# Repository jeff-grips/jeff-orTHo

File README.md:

# jeff-orTHo
 through-hole ortho board

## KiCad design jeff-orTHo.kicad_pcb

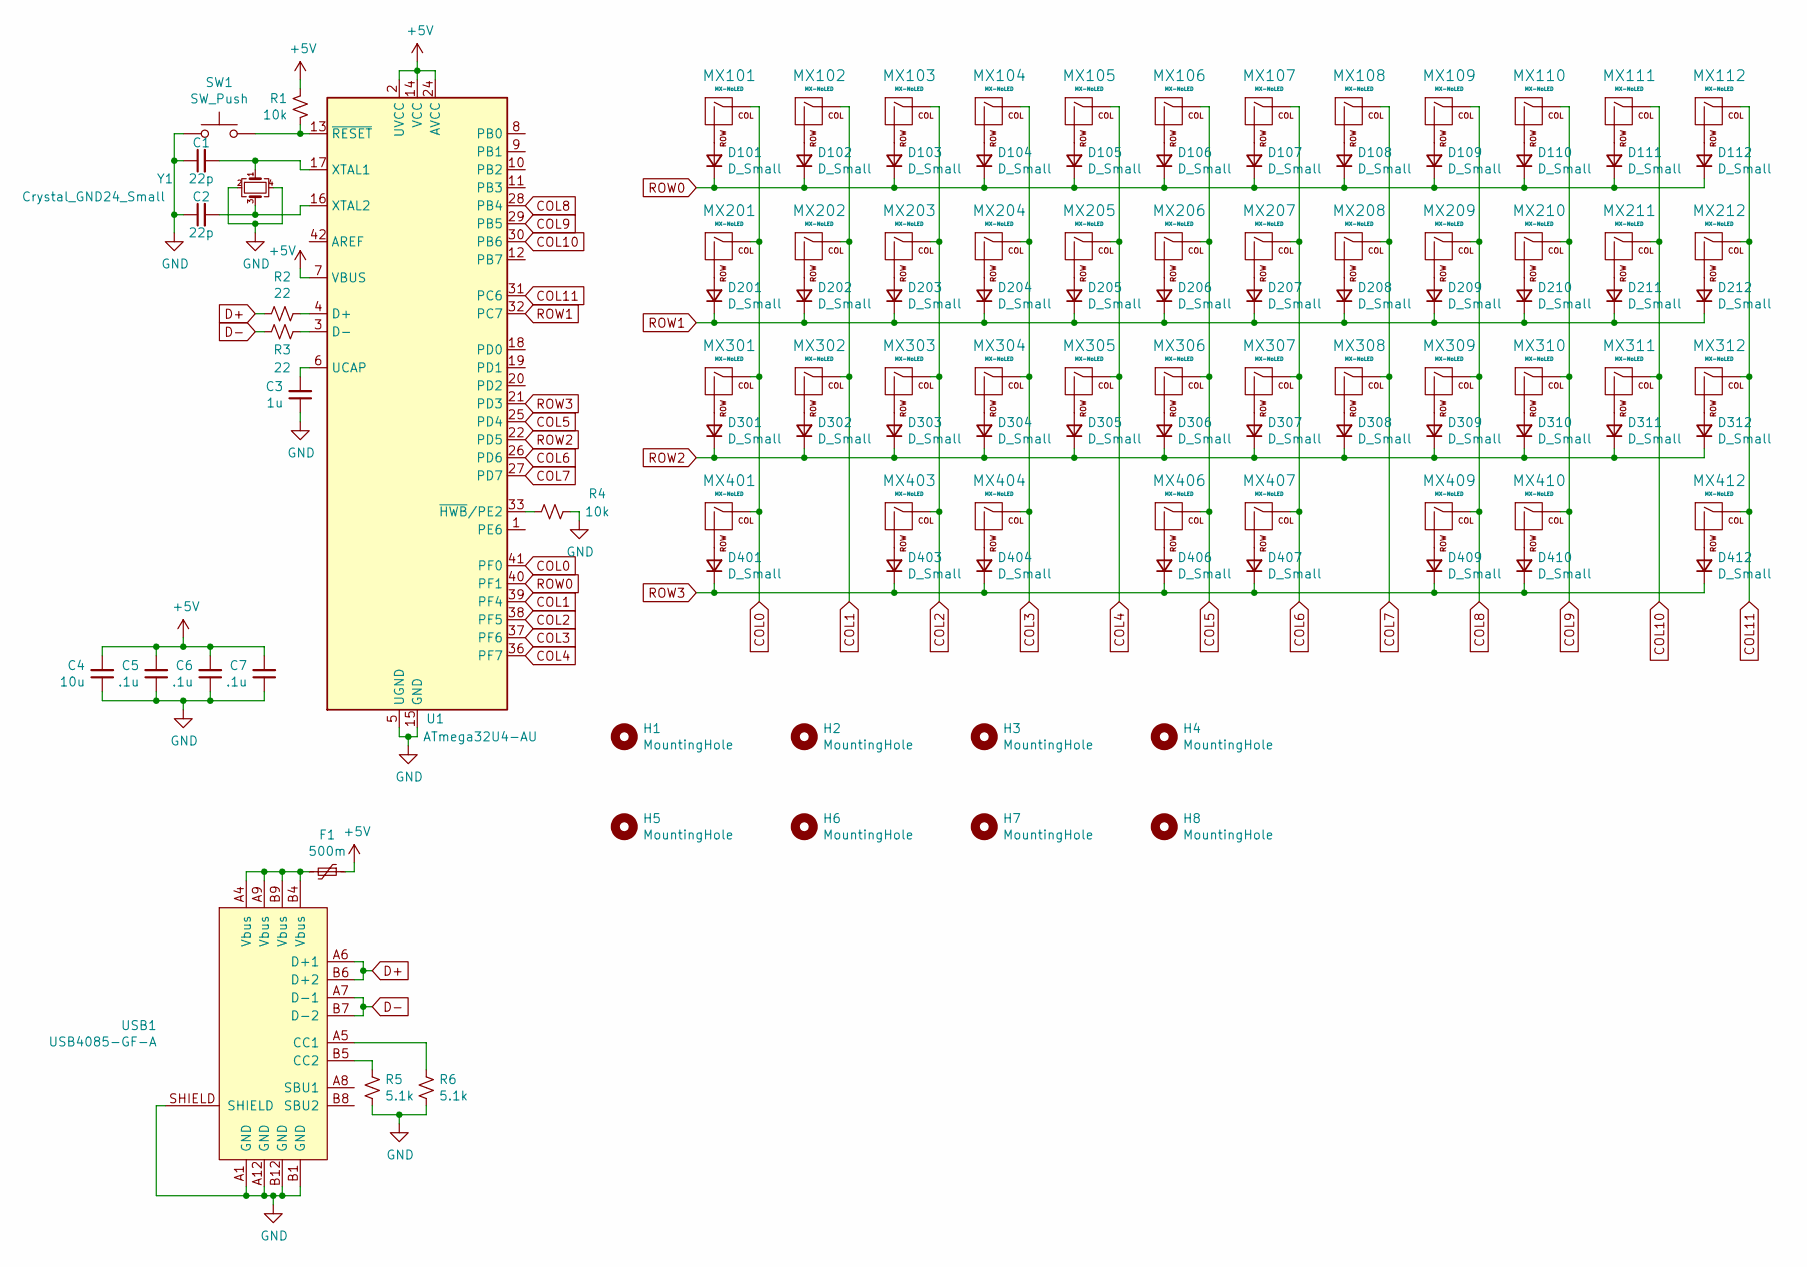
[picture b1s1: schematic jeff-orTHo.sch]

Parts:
C1, C2: 22p; C_1206_3216Metric_Pad1.33x1.80mm_HandSolder
C3: 1u; C_1206_3216Metric_Pad1.33x1.80mm_HandSolder
C4: 10u; C_1206_3216Metric_Pad1.33x1.80mm_HandSolder
C5, C6, C7: .1u; C_1206_3216Metric_Pad1.33x1.80mm_HandSolder
D101, D102, D103, D104, D105, D106, D107, D108, D109, D110, D111, D112, D201, D202, D203, D204, D205, D206, D207, D208, D209, D210, D211, D212, D301, D302, D303, D304, D305, D306, D307, D308, D309, D310, D311, D312, D401, D403, D404, D406, D407, D409, D410, D412: D_Small; D_SOD-123
F1: 500m; Fuse_1206_3216Metric_Pad1.42x1.75mm_HandSolder
H1, H2, H3, H4, H5, H6, H7, H8: MountingHole; MountingHole_2.2mm_M2
MX101, MX102, MX103, MX104, MX105, MX106, MX107, MX108, MX109, MX110, MX111, MX112, MX201, MX202, MX203, MX204, MX205, MX206, MX207, MX208, MX209, MX210, MX211, MX212, MX301, MX302, MX303, MX304, MX305, MX306, MX307, MX308, MX309, MX310, MX311, MX312: MX-NoLED; MX-1U-NoLED
MX401, MX403, MX404, MX406, MX407, MX409, MX410, MX412: MX-NoLED; MX-1.5U-NoLED
R1, R4: 10k; R_1206_3216Metric_Pad1.30x1.75mm_HandSolder
R2, R3: 22; R_1206_3216Metric_Pad1.30x1.75mm_HandSolder
R5, R6: 5.1k; R_1206_3216Metric_Pad1.30x1.75mm_HandSolder
SW1: SW_Push; SKQG-1155865
U1: ATmega32U4-AU; TQFP-44_10x10mm_P0.8mm
USB1: USB4085-GF-A
Y1: Crystal_GND24_Small; Crystal_SMD_3225-4Pin_3.2x2.5mm_HandSoldering

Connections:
+5V: C4.2, C5.2, C6.2, C7.2, F1.1, R1.2, U1.2 (UVCC), U1.7 (VBUS), U1.14 (VCC), U1.24 (AVCC), U1.34 (VCC), U1.44 (AVCC)
COL0: MX101.1 (COL), MX201.1 (COL), MX301.1 (COL), MX401.1 (COL), U1.41 (PF0)
COL1: MX102.1 (COL), MX202.1 (COL), MX302.1 (COL), U1.39 (PF4)
COL2: MX103.1 (COL), MX203.1 (COL), MX303.1 (COL), MX403.1 (COL), U1.38 (PF5)
COL3: MX104.1 (COL), MX204.1 (COL), MX304.1 (COL), MX404.1 (COL), U1.37 (PF6)
COL4: MX105.1 (COL), MX205.1 (COL), MX305.1 (COL), U1.36 (PF7)
COL5: MX106.1 (COL), MX206.1 (COL), MX306.1 (COL), MX406.1 (COL), U1.25 (PD4)
COL6: MX107.1 (COL), MX207.1 (COL), MX307.1 (COL), MX407.1 (COL), U1.26 (PD6)
COL7: MX108.1 (COL), MX208.1 (COL), MX308.1 (COL), U1.27 (PD7)
COL8: MX109.1 (COL), MX209.1 (COL), MX309.1 (COL), MX409.1 (COL), U1.28 (PB4)
COL9: MX110.1 (COL), MX210.1 (COL), MX310.1 (COL), MX410.1 (COL), U1.29 (PB5)
COL10: MX111.1 (COL), MX211.1 (COL), MX311.1 (COL), U1.30 (PB6)
COL11: MX112.1 (COL), MX212.1 (COL), MX312.1 (COL), MX412.1 (COL), U1.31 (PC6)
D+: R2.2, USB1.A6 (D+1), USB1.B6 (D+2)
D-: R3.2, USB1.A7 (D-1), USB1.B7 (D-2)
GND: C1.1, C2.1, C3.1, C4.1, C5.1, C6.1, C7.1, R4.1, R5.2, R6.2, SW1.1, U1.5 (UGND), U1.15 (GND), U1.23 (GND), U1.35 (GND), U1.43 (GND), USB1.A1 (GND), USB1.A12 (GND), USB1.B1 (GND), USB1.B12 (GND), USB1.SHIELD, Y1.2, Y1.4
unnamed: C1.2, U1.17 (XTAL1), Y1.1
unnamed: C2.2, U1.16 (XTAL2), Y1.3
unnamed: C3.2, U1.6 (UCAP)
unnamed: D101.2 (A), MX101.2 (ROW)
unnamed: D102.2 (A), MX102.2 (ROW)
unnamed: D103.2 (A), MX103.2 (ROW)
unnamed: D104.2 (A), MX104.2 (ROW)
unnamed: D105.2 (A), MX105.2 (ROW)
unnamed: D106.2 (A), MX106.2 (ROW)
unnamed: D107.2 (A), MX107.2 (ROW)
unnamed: D108.2 (A), MX108.2 (ROW)
unnamed: D109.2 (A), MX109.2 (ROW)
unnamed: D110.2 (A), MX110.2 (ROW)
unnamed: D111.2 (A), MX111.2 (ROW)
unnamed: D112.2 (A), MX112.2 (ROW)
unnamed: D201.2 (A), MX201.2 (ROW)
unnamed: D202.2 (A), MX202.2 (ROW)
unnamed: D203.2 (A), MX203.2 (ROW)
unnamed: D204.2 (A), MX204.2 (ROW)
unnamed: D205.2 (A), MX205.2 (ROW)
unnamed: D206.2 (A), MX206.2 (ROW)
unnamed: D207.2 (A), MX207.2 (ROW)
unnamed: D208.2 (A), MX208.2 (ROW)
unnamed: D209.2 (A), MX209.2 (ROW)
unnamed: D210.2 (A), MX210.2 (ROW)
unnamed: D211.2 (A), MX211.2 (ROW)
unnamed: D212.2 (A), MX212.2 (ROW)
unnamed: D301.2 (A), MX301.2 (ROW)
unnamed: D302.2 (A), MX302.2 (ROW)
unnamed: D303.2 (A), MX303.2 (ROW)
unnamed: D304.2 (A), MX304.2 (ROW)
unnamed: D305.2 (A), MX305.2 (ROW)
unnamed: D306.2 (A), MX306.2 (ROW)
unnamed: D307.2 (A), MX307.2 (ROW)
unnamed: D308.2 (A), MX308.2 (ROW)
unnamed: D309.2 (A), MX309.2 (ROW)
unnamed: D310.2 (A), MX310.2 (ROW)
unnamed: D311.2 (A), MX311.2 (ROW)
unnamed: D312.2 (A), MX312.2 (ROW)
unnamed: D401.2 (A), MX401.2 (ROW)
unnamed: D403.2 (A), MX403.2 (ROW)
unnamed: D404.2 (A), MX404.2 (ROW)
unnamed: D406.2 (A), MX406.2 (ROW)
unnamed: D407.2 (A), MX407.2 (ROW)
unnamed: D409.2 (A), MX409.2 (ROW)
unnamed: D410.2 (A), MX410.2 (ROW)
unnamed: D412.2 (A), MX412.2 (ROW)
unnamed: F1.2, USB1.A4 (Vbus), USB1.A9 (Vbus), USB1.B4 (Vbus), USB1.B9 (Vbus)
unnamed: R1.1, SW1.2, U1.13 (~RESET)
unnamed: R2.1, U1.4 (D+)
unnamed: R3.1, U1.3 (D-)
unnamed: R4.2, U1.33 (~HWB~/PE2)
unnamed: R5.1, USB1.B5 (CC2)
unnamed: R6.1, USB1.A5 (CC1)
ROW0: D101.1 (K), D102.1 (K), D103.1 (K), D104.1 (K), D105.1 (K), D106.1 (K), D107.1 (K), D108.1 (K), D109.1 (K), D110.1 (K), D111.1 (K), D112.1 (K), U1.40 (PF1)
ROW1: D201.1 (K), D202.1 (K), D203.1 (K), D204.1 (K), D205.1 (K), D206.1 (K), D207.1 (K), D208.1 (K), D209.1 (K), D210.1 (K), D211.1 (K), D212.1 (K), U1.32 (PC7)
ROW2: D301.1 (K), D302.1 (K), D303.1 (K), D304.1 (K), D305.1 (K), D306.1 (K), D307.1 (K), D308.1 (K), D309.1 (K), D310.1 (K), D311.1 (K), D312.1 (K), U1.22 (PD5)
ROW3: D401.1 (K), D403.1 (K), D404.1 (K), D406.1 (K), D407.1 (K), D409.1 (K), D410.1 (K), D412.1 (K), U1.21 (PD3)

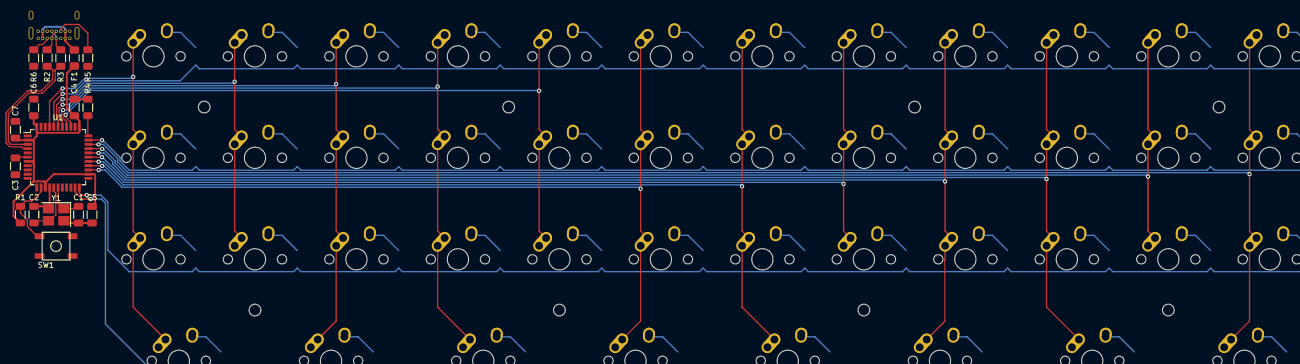
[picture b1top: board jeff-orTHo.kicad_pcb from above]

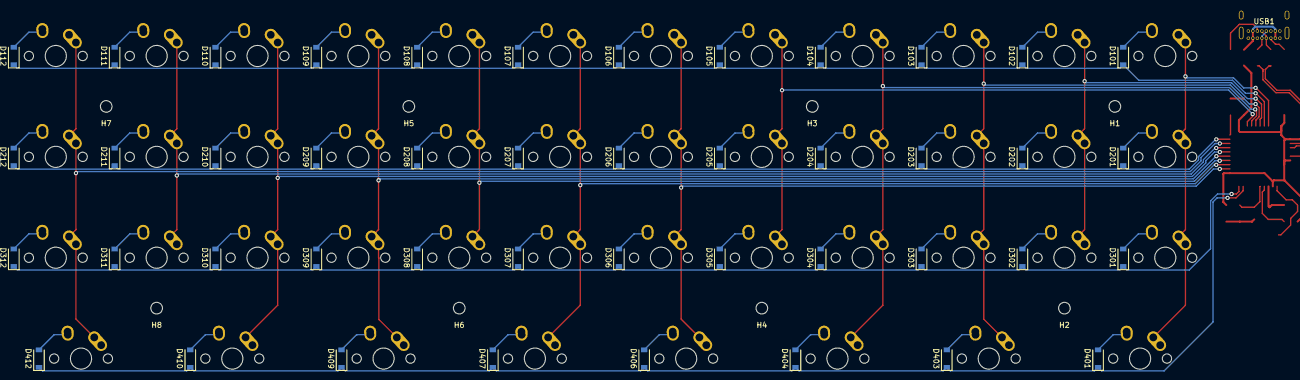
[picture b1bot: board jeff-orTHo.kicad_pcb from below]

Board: 2 copper layers, 114 parts (53 on the bottom side), 74 nets.

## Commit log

2021-02-03 Initialization
    Initialize KiCad project
2021-02-03 Add submodules
2021-02-03 Add footprint libraries
2021-02-03 schematic
    just kidding it's not through hole anymore
2021-02-03 Initial layout
2021-02-03 Routing
    Layout tweaks, need ground/power fills
